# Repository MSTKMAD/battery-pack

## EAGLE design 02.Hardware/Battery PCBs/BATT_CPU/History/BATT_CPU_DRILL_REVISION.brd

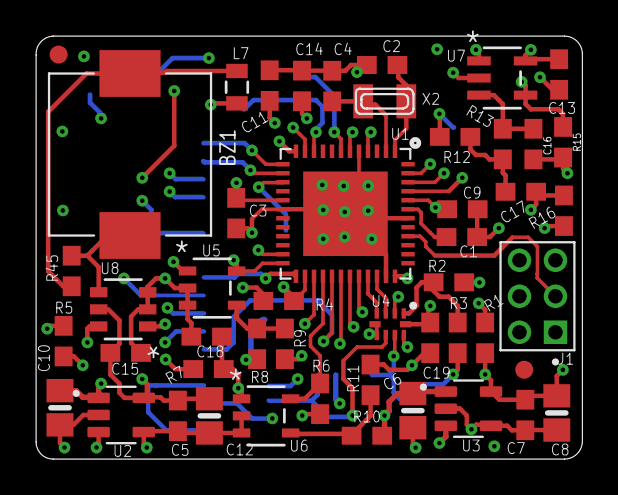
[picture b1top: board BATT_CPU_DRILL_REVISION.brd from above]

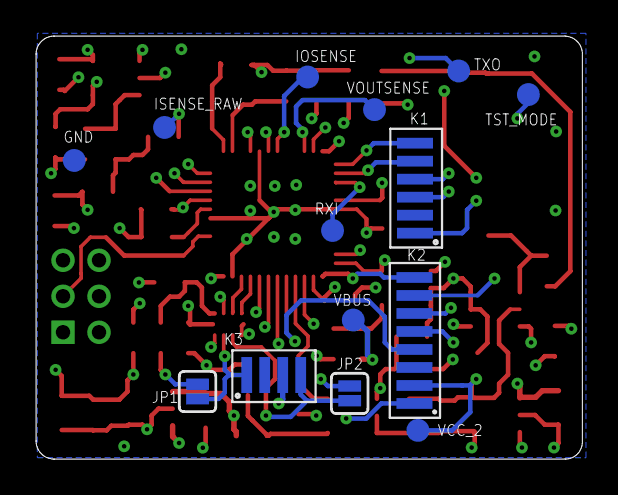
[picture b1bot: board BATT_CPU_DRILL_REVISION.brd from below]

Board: 4 copper layers, 30.4 x 23.5 mm, 63 parts (14 on the bottom side), 44 nets.

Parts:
BZ1: PKMCS0909E4000-R1; PKMCS0909
C1, C14: 2.2uF; 0603-NO
C2, C4: 22pF; 0603-NO
C3, C5, C7, C9, C11, C13, C15, C18, C19: 100n; 0603-NO
C6, C8, C10, C12: 2.2uF; 0805-NO
C16, C17: 1u; 0603-NO
GND: TESTPAD_TPSQB1,27; TESTPAD_B1,27
IOSENSE: TESTPAD_TPSQB1,27; TESTPAD_B1,27
ISENSE_RAW: TESTPAD_TPSQB1,27; TESTPAD_B1,27
J1: 2314820-6; TE_2314820-6
JP1, JP2: JUMPER-SMT_2_NO_SILK; SMT-JUMPER_2_NO_SILK
K1: FLEX_DISPL; FLEX6
K2: FLEX_DCDC; FLEX8
K3: FLEX_CONN; FLEX4
L7: MMZ2012Y202BT000; 0805
R1, R2: 2k2; 0603
R3, R4: 100R; 0603
R5: 100k; 0603
R6, R7, R8, R10: 120k; 0603
R9: 5.6k; 0603
R11: 8.2k; 0603
R12, R15: 2.4k; 0603
R13: 62k; 0603
R16: 36k; 0603
R45: 330; 0603
RXI: TESTPAD_TPSQB1,27; TESTPAD_B1,27
TST_MODE: TESTPAD_TPSQB1,27; TESTPAD_B1,27
TXO: TESTPAD_TPSQB1,27; TESTPAD_B1,27
U1: ATSAMD21G18_QFN; TQFN48_7MM
U2, U3: TPS78230DDCR; SOT95P280X110-5N
U4: TS3USB221A; QFN-10-RSE
U5, U6: MAX9062EUK+T; 21-0057F_MXM
U7: MCP6071T-E/OT; SOT-23-5_MC_MCH
U8: SN74LVC1G19DBVR; DBV6
U$34, U$35: FIDUCIAL""; FIDUCIAL_1MM
VBUS: TESTPAD_TPSQB1,27; TESTPAD_B1,27
VCC_2: TESTPAD_TPSQB1,27; TESTPAD_B1,27
VOUTSENSE: TESTPAD_TPSQB1,27; TESTPAD_B1,27
X2: 32.768; XTAL3215

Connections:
!RESET: J1.3, U1.40
#EN_DCDC: K2.8, U1.25
/FLAG_BATTLOW: R6.1, U1.28, U6.5
AREF: C14.1, U1.4
BUZZER: U1.23, U8.1
D+: U1.34, U4.3
D-: U1.33, U4.4
EN_VCC2: R5.2, U2.3
FLAG_CHRG: R7.1, U1.24, U5.5
GND: C1.2, C2.2, C3.2, C4.2, C5.2, C6.2, C7.2, C8.2, C9.2, C10.2, C11.2, C12.2, C13.2, C14.2, C15.2, C16.2, C18.2, C19.2, GND.TP, J1.5, K1.2, K2.3, K3.2, R5.1, R9.2, R11.2, R15.2, U1.5, U1.18, U1.35, U1.42, U1.THERMAL, U2.2, U2.4, U3.2, U3.4, U4.5, U4.6, U5.2, U5.3, U6.2, U6.3, U7.2, U8.2, U8.3
IOSENSE: C17.2, IOSENSE.TP, R16.1, U1.7, U1.47, U7.1
ISENSE_RAW: ISENSE_RAW.TP, K2.5, R12.2
unnamed: R15.1, R16.2, U7.4
unnamed: R2.1, R3.1, U4.1
unnamed: R1.1, R4.1, U4.2
unnamed: C2.1, U1.1, X2.P$1
unnamed: C4.1, U1.2, X2.P$2
unnamed: C17.1, R12.1, R13.2
unnamed: R10.1, R11.1, U6.4
unnamed: R8.1, R9.1, U5.4
unnamed: C16.1, R13.1, U7.3
unnamed: L7.1, U8.6
unnamed: BZ1.1, L7.2, R45.1
unnamed: BZ1.2, R45.2, U8.4
OP_SWITCH: K2.4, U1.29
RXI: RXI.TP, U1.15
SCL: K1.4, K2.6, U1.32
SCL2_CPU: JP2.1, R4.2, U1.26
SCL_2: JP2.2, K3.4, U4.7
SDA: K1.3, K2.1, U1.31
SDA2_CPU: JP1.1, R3.2, U1.27
SDA_2: JP1.2, K3.1, U4.8
SWCLK: J1.4, U1.45
SWDIO: J1.2, U1.46
S_DOWN: K1.6, U1.13
S_UP: K1.5, U1.14
TST_MODE: TST_MODE.TP, U1.12
TXO: TXO.TP, U1.11
USB_SEL: U1.30, U4.9
VBUS: C6.1, C10.1, K3.3, R8.2, R10.2, U2.1, U3.1, U3.3, VBUS.TP
VCC: C3.1, C7.1, C8.1, C9.1, C11.1, C18.1, C19.1, J1.1, R1.2, R2.2, R6.2, R7.2, U1.6, U1.17, U1.36, U1.44, U3.5, U4.10, U5.1, U6.1
VCC_2: C5.1, C12.1, C13.1, C15.1, K1.1, K2.2, U2.5, U7.5, U8.5, VCC_2.TP
VDDCORE: C1.1, U1.43
VOUTSENSE: K2.7, U1.10, VOUTSENSE.TP

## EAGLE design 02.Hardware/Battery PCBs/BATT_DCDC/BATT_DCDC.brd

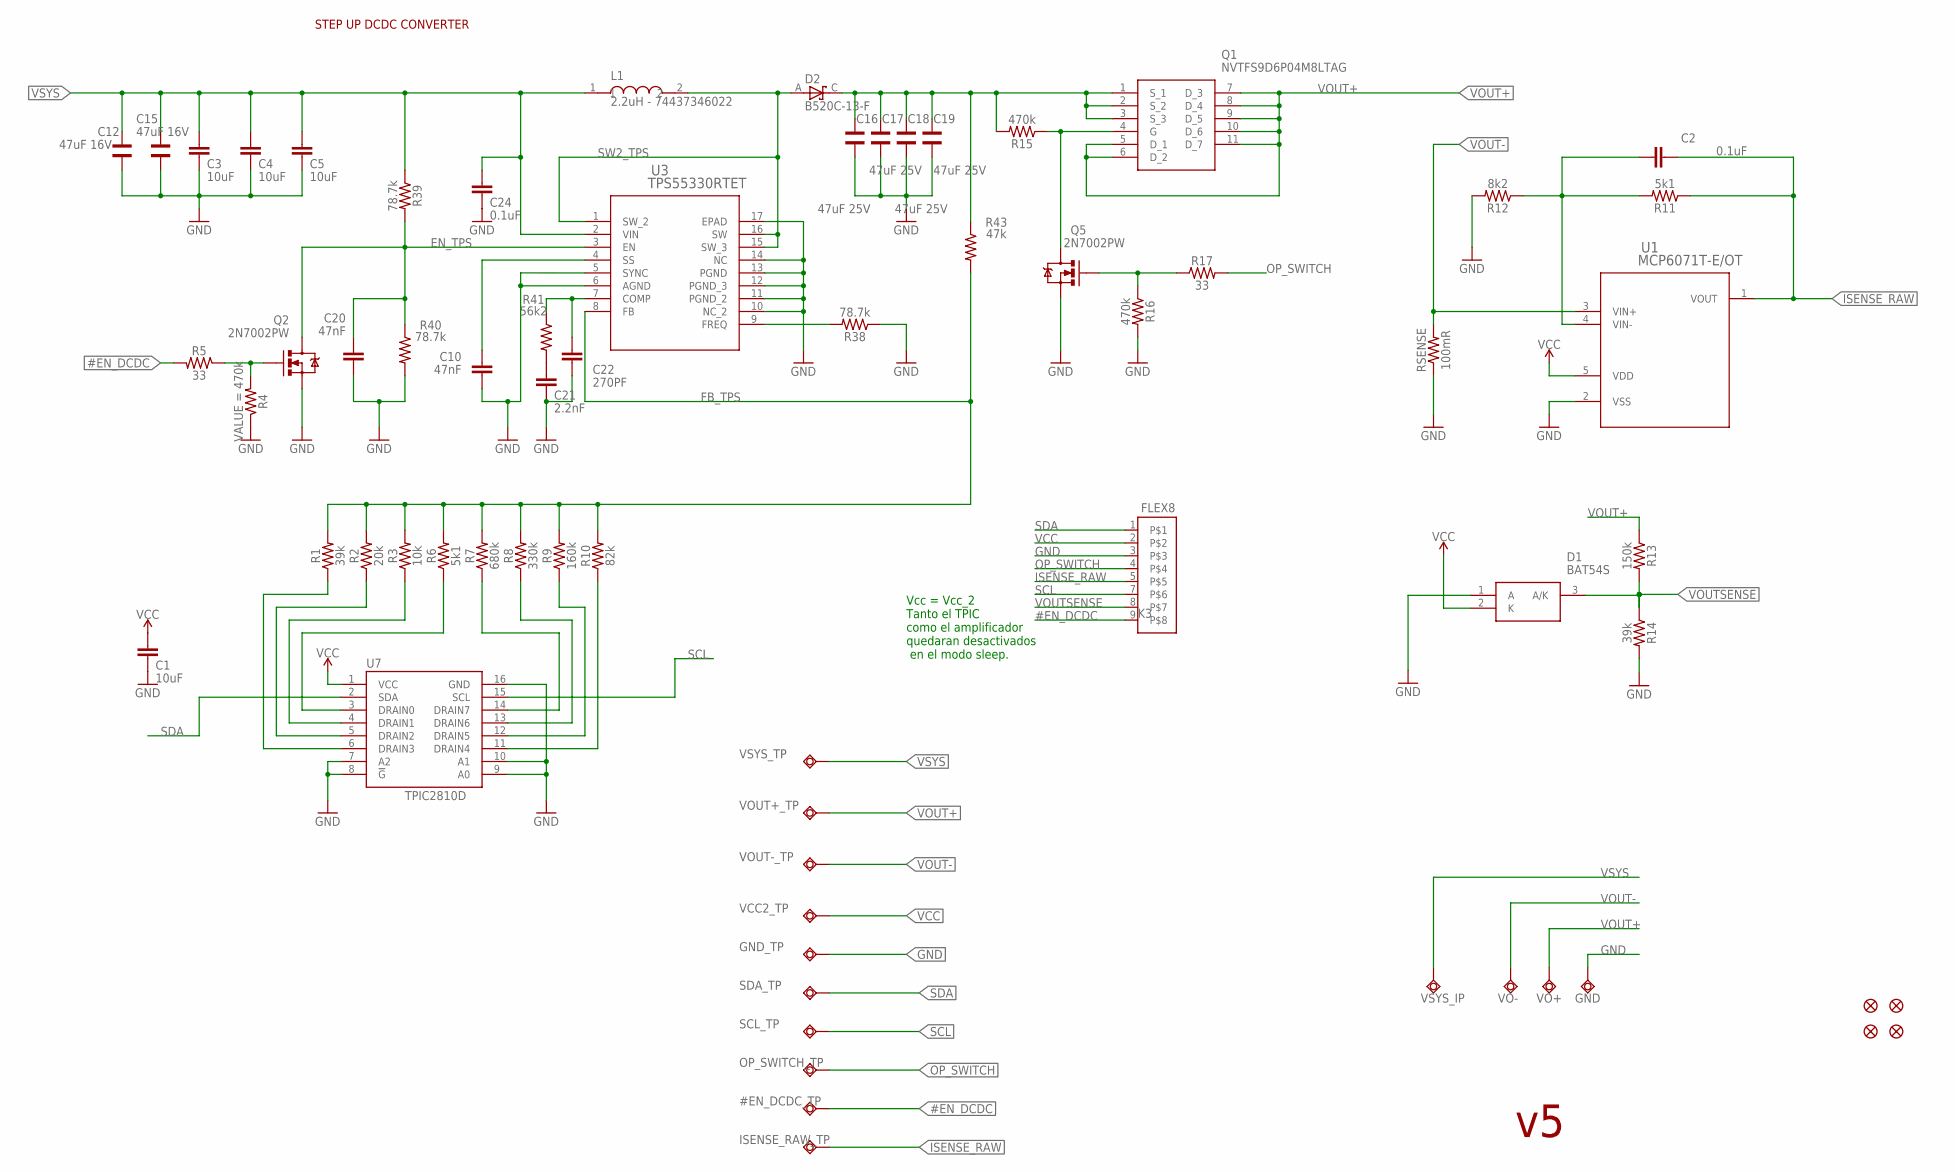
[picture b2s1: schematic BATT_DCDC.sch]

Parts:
#EN_DCDC_TP: TESTPAD_TPSQB1,27; TESTPAD_B1,27
C1, C3, C4, C5: 10uF; 0805
C2, C24: 0.1uF; 0603
C10, C20: 47nF; 0603
C12, C15: 47uF 16V; WCAP-CSGP_1210
C16, C17, C18, C19: 47uF 25V; WCAP-CSGP_1210
C21: 2.2nF; 0603
C22: 270PF; 0603
D1: BAT54S; SOT95P240X110-3N
D2: B520C-13-F; DIOM7959X250N
GND: TESTPAD_TPSQTP15SQ; TESTPAD_TP15SQ
GND_TP: TESTPAD_TPSQB1,27; TESTPAD_B1,27
ISENSE_RAW_TP: TESTPAD_TPSQB1,27; TESTPAD_B1,27
K3: FLEX8
L1: 2.2uH - 74437346022; INDM7366X500
OP_SWITCH_TP: TESTPAD_TPSQB1,27; TESTPAD_B1,27
Q1: NVTFS9D6P04M8LTAG; NVTFS5124PLTWG
Q2, Q5: 2N7002PW; SOT323
R1, R14: 39k; 0402
R2: 20k; 0402
R3: 10k; 0402
R4, R15, R16: 470k; 0402
R5, R17: 33; 0402
R6, R11: 5k1; 0402
R7: 680k; 0402
R8: 330k; 0402
R9: 160k; 0402
R10: 82k; 0402
R12: 8k2; 0402
R13: 150k; 0402
R38, R39, R40: 78.7k; 0402
R41: 56k2; 0402
R43: 47k; 0402
RSENSE: 100mR; 0603
SCL_TP: TESTPAD_TPSQB1,27; TESTPAD_B1,27
SDA_TP: TESTPAD_TPSQB1,27; TESTPAD_B1,27
U1: MCP6071T-E/OT; SOT-23-5_MC_MCH
U3: TPS55330RTET; RTE16_1P66X1P66_TEX
U7: TPIC2810D; SO16
U$1, U$2, U$34, U$35: FIDUCIAL""; FIDUCIAL_1MM
VCC2_TP: TESTPAD_TPSQB1,27; TESTPAD_B1,27
VO+: TESTPAD_TPSQTP15SQ; TESTPAD_TP15SQ
VO-: TESTPAD_TPSQTP15SQ; TESTPAD_TP15SQ
VOUT+_TP: TESTPAD_TPSQB1,27; TESTPAD_B1,27
VOUT-_TP: TESTPAD_TPSQB1,27; TESTPAD_B1,27
VSYS_IP: TESTPAD_TPSQTP15SQ; TESTPAD_TP15SQ
VSYS_TP: TESTPAD_TPSQB1,27; TESTPAD_B1,27

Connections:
#EN_DCDC: #EN_DCDC_TP.TP, K3.9, R5.2
COMP_TPS: C22.2, R41.1, U3.7 (COMP)
EN_TPS: C20.1, Q2.3 (D), R39.2, R40.1, U3.3 (EN)
FB_TPS: R1.2, R2.2, R3.2, R6.2, R7.2, R8.2, R9.2, R10.2, R43.2, U3.8 (FB)
FREQ_TPS: R38.2, U3.9 (FREQ)
GND: C1.1, C3.1, C4.1, C5.1, C10.2, C12.1, C15.1, C16.1, C17.1, C18.1, C19.1, C20.2, C21.1, C22.1, C24.1, D1.1 (A), GND.TP, GND_TP.TP, K3.3, Q2.2 (S), Q5.2 (S), R4.1, R12.2, R14.2, R16.2, R38.1, R40.2, RSENSE.1, U1.2 (VSS), U3.5 (SYNC), U3.6 (AGND), U3.10 (NC_2), U3.11 (PGND_2), U3.12 (PGND_3), U3.13 (PGND), U3.14 (NC), U3.17 (EPAD), U7.7 (A2), U7.8 (!G), U7.9 (A0), U7.10 (A1), U7.16 (GND)
ISENSE_RAW: C2.1, ISENSE_RAW_TP.TP, K3.5, R11.1, U1.1 (VOUT)
unnamed: C2.2, R11.2, R12.1, U1.4 (VIN-)
unnamed: R1.1, U7.6 (DRAIN3)
unnamed: R2.1, U7.5 (DRAIN2)
unnamed: Q2.1 (G), R4.2, R5.1
unnamed: R3.1, U7.4 (DRAIN1)
unnamed: R6.1, U7.3 (DRAIN0)
unnamed: R7.1, U7.14 (DRAIN7)
unnamed: Q1.4 (G), Q5.3 (D), R15.1
unnamed: R8.1, U7.13 (DRAIN6)
unnamed: R9.1, U7.12 (DRAIN5)
unnamed: R10.1, U7.11 (DRAIN4)
unnamed: Q5.1 (G), R16.1, R17.1
unnamed: C10.1, U3.4 (SS)
unnamed: C21.2, R41.2
OP_SWITCH: K3.4, OP_SWITCH_TP.TP, R17.2
SCL: K3.7, SCL_TP.TP, U7.15 (SCL)
SDA: K3.1, SDA_TP.TP, U7.2 (SDA)
SW2_TPS: D2.A, L1.2, U3.1 (SW_2), U3.15 (SW_3), U3.16 (SW)
VCC: C1.2, D1.2 (K), K3.2, U1.5 (VDD), U7.1 (VCC), VCC2_TP.TP
VOUT+: Q1.5 (D_1), Q1.6 (D_2), Q1.7 (D_3), Q1.8 (D_4), Q1.9 (D_5), Q1.10 (D_6), Q1.11 (D_7), R13.1, VO+.TP, VOUT+_TP.TP
VOUT-: RSENSE.2, U1.3 (VIN+), VO-.TP, VOUT-_TP.TP
VOUTSENSE: D1.3 (A/K), K3.8, R13.2, R14.1
VSOURCE: C16.2, C17.2, C18.2, C19.2, D2.C, Q1.1 (S_1), Q1.2 (S_2), Q1.3 (S_3), R15.2, R43.1
VSYS: C3.2, C4.2, C5.2, C12.2, C15.2, C24.2, L1.1, R39.1, U3.2 (VIN), VSYS_IP.TP, VSYS_TP.TP

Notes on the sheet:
STEP UP DCDC CONVERTER
Vcc = Vcc_2 Tanto el TPIC como el amplificador quedaran desactivados en el modo sleep.

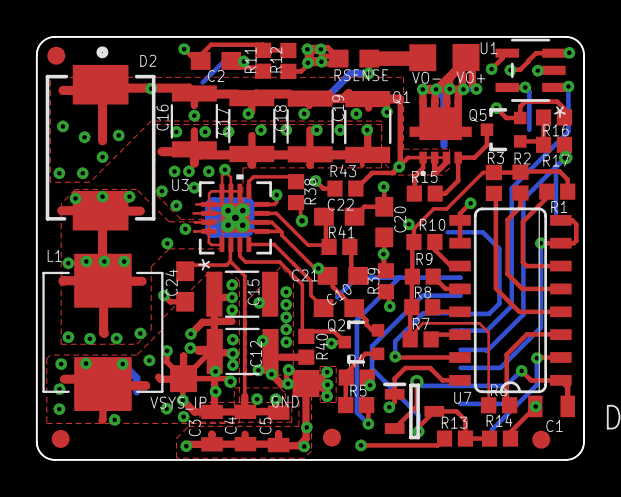
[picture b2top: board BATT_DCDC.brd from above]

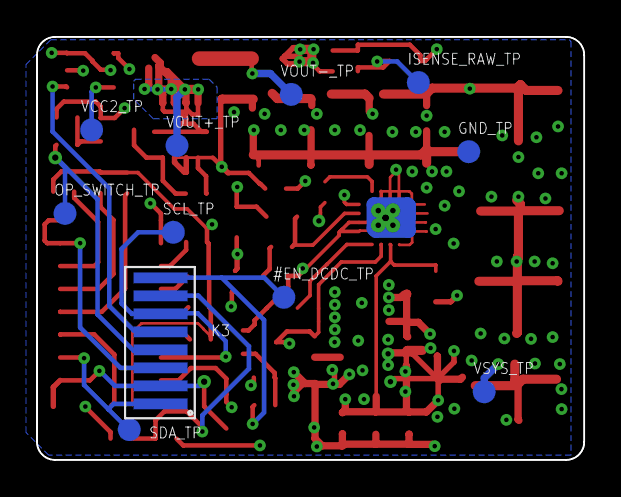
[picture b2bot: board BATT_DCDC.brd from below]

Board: 4 copper layers, 30.4 x 23.5 mm, 67 parts (11 on the bottom side), 31 nets.

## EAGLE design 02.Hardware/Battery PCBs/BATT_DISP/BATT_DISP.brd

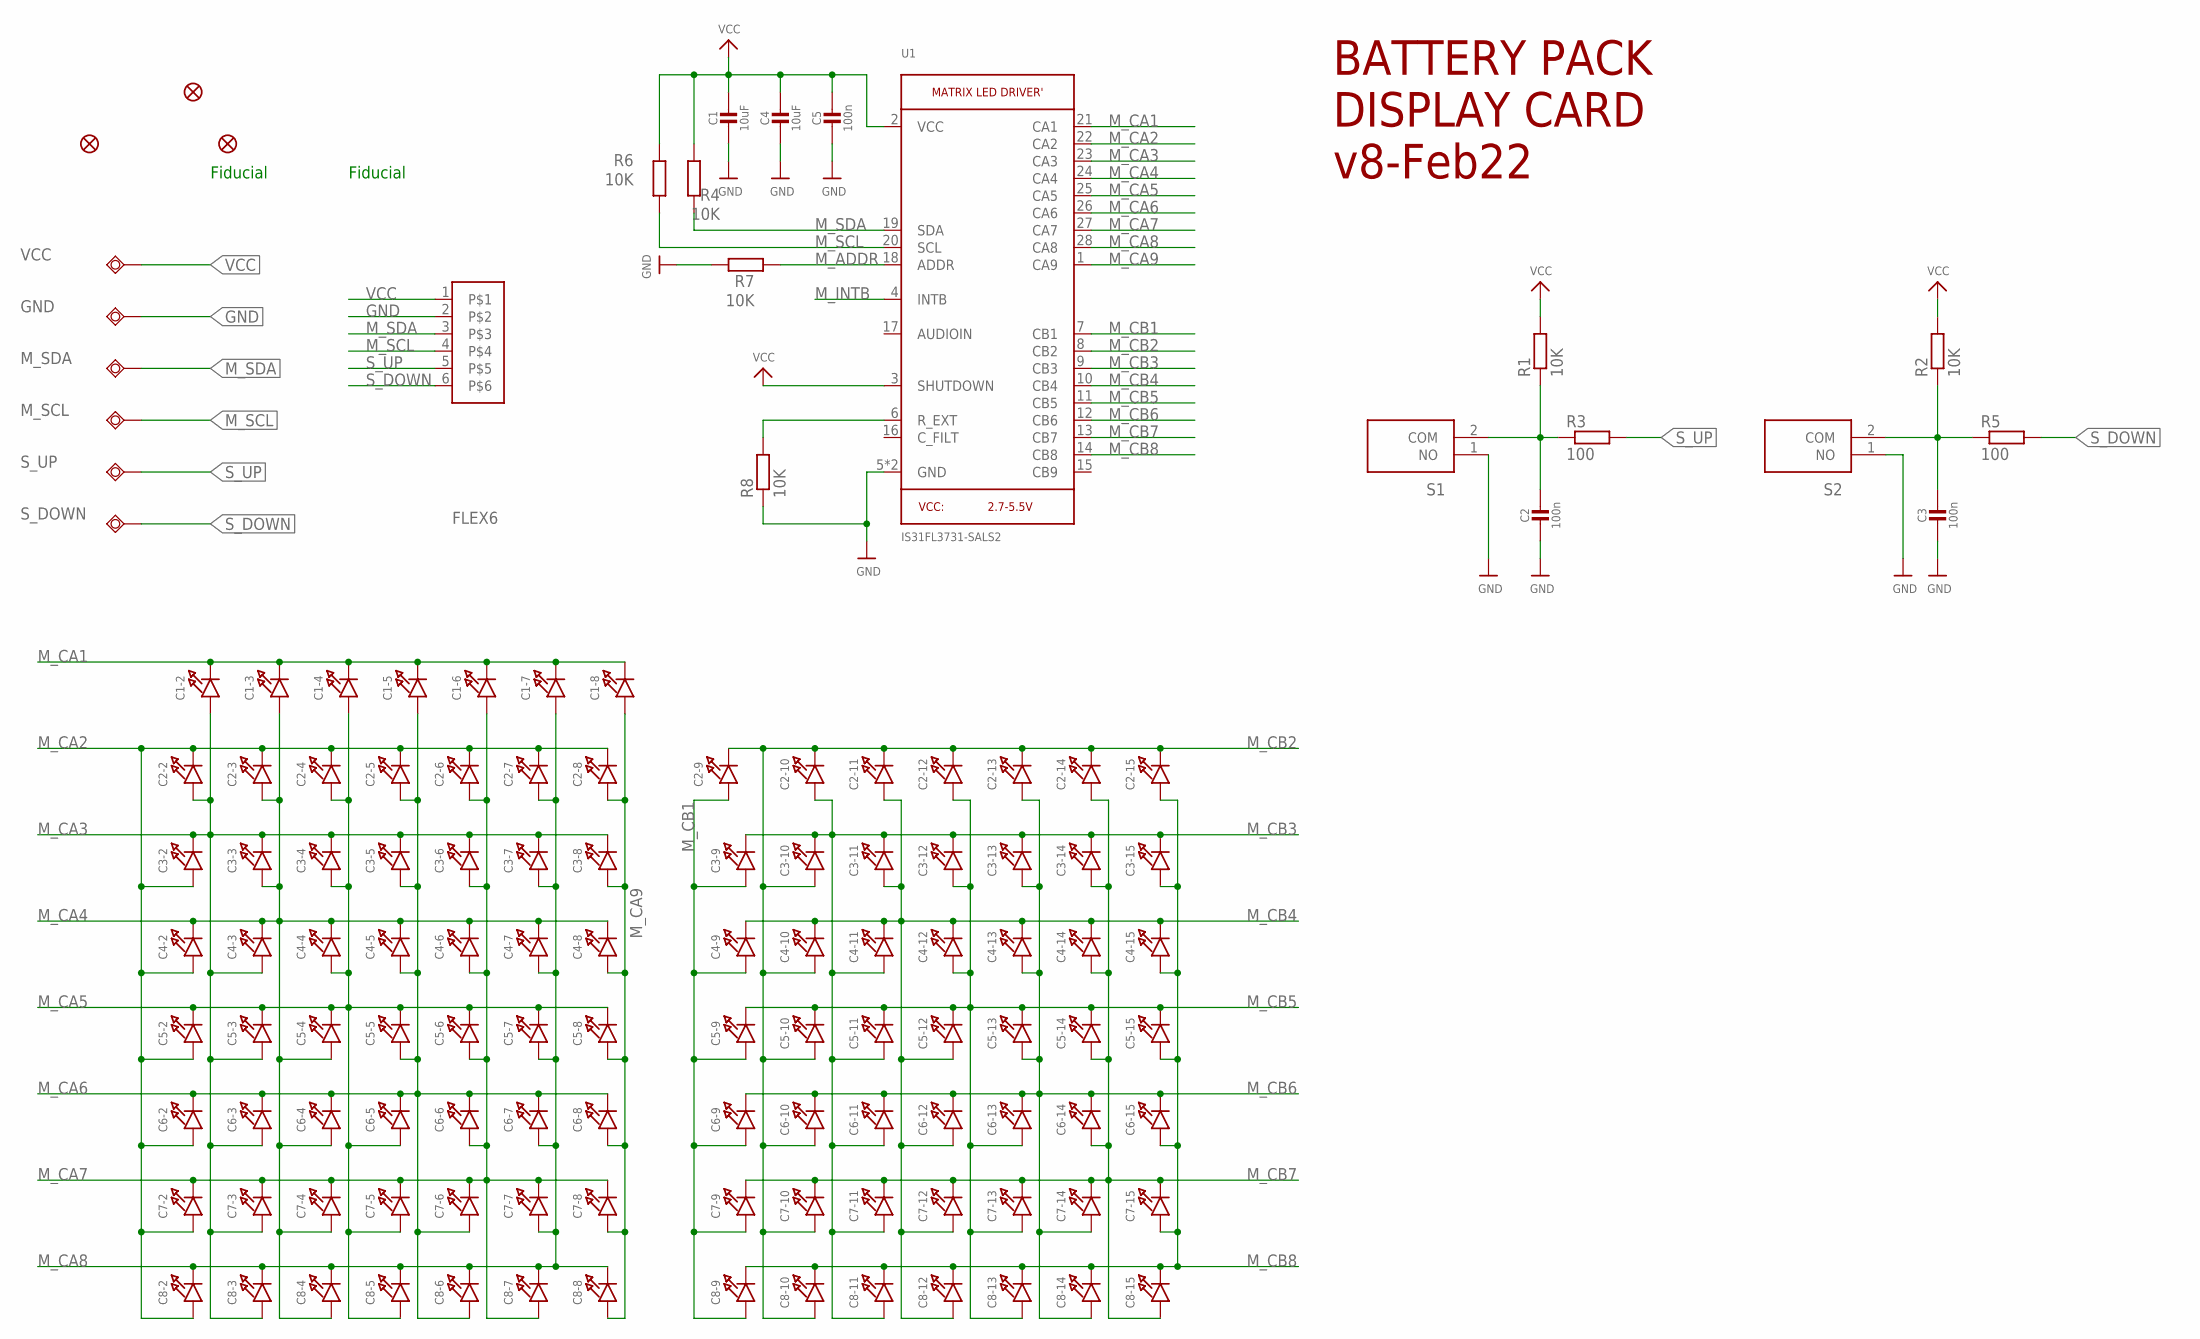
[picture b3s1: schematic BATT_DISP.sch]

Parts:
C1, C4: 10uF; 0805-NO
C1-2, C1-3, C1-4, C1-5, C1-6, C1-7, C1-8, C2-2, C2-3, C2-4, C2-5, C2-6, C2-7, C2-8, C2-9, C2-10, C2-11, C2-12, C2-13, C2-14, C2-15, C3-2, C3-3, C3-4, C3-5, C3-6, C3-7, C3-8, C3-9, C3-10, C3-11, C3-12, C3-13, C3-14, C3-15, C4-2, C4-3, C4-4, C4-5, C4-6, C4-7, C4-8, C4-9, C4-10, C4-11, C4-12, C4-13, C4-14, C4-15, C5-2, C5-3, C5-4, C5-5, C5-6, C5-7, C5-8, C5-9, C5-10, C5-11, C5-12, C5-13, C5-14, C5-15, C6-2, C6-3, C6-4, C6-5, C6-6, C6-7, C6-8, C6-9, C6-10, C6-11, C6-12, C6-13, C6-14, C6-15, C7-2, C7-3, C7-4, C7-5, C7-6, C7-7, C7-8, C7-9, C7-10, C7-11, C7-12, C7-13, C7-14, C7-15, C8-2, C8-3, C8-4, C8-5, C8-6, C8-7, C8-8, C8-9, C8-10, C8-11, C8-12, C8-13, C8-14, C8-15: LED0402_NOOUTLINE; CHIPLED_0402_NOOUTLINE
C2, C3, C5: 100n; 0805-NO
FD1: FIDUCIALUFIDUCIAL; FIDUCIAL-MICRO
FD2, FD3: FIDUCIAL""; FIDUCIAL_1MM
GND: TESTPAD_TPSQB1,27; TESTPAD_B1,27
K1: FLEX6
M_SCL: TESTPAD_TPSQB1,27; TESTPAD_B1,27
M_SDA: TESTPAD_TPSQB1,27; TESTPAD_B1,27
R1, R2, R4, R6, R7, R8: 10K; R0603
R3, R5: 100; R0603
S1, S2: KXT311LHS
S_DOWN: TESTPAD_TPSQB1,27; TESTPAD_B1,27
S_UP: TESTPAD_TPSQB1,27; TESTPAD_B1,27
U1: IS31FL3731-SALS2; QFN28_4MM_0.4MM
VCC: TESTPAD_TPSQB1,27; TESTPAD_B1,27

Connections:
GND: C1.2, C2.2, C3.2, C4.2, C5.2, GND.TP, K1.2, R7.2, R8.1, S1.1 (NO), S2.1 (NO), U1.5 (GND), U1.THERMAL (GND)
M_ADDR: R7.1, U1.18 (ADDR)
M_CA1: C1-2.C, C1-3.C, C1-4.C, C1-5.C, C1-6.C, C1-7.C, C1-8.C, U1.21 (CA1)
M_CA2: C2-2.C, C2-3.C, C2-4.C, C2-5.C, C2-6.C, C2-7.C, C2-8.C, C3-2.A, C4-2.A, C5-2.A, C6-2.A, C7-2.A, C8-2.A, U1.22 (CA2)
M_CA3: C1-2.A, C2-2.A, C3-2.C, C3-3.C, C3-4.C, C3-5.C, C3-6.C, C3-7.C, C3-8.C, C4-3.A, C5-3.A, C6-3.A, C7-3.A, C8-3.A, U1.23 (CA3)
M_CA4: C1-3.A, C2-3.A, C3-3.A, C4-2.C, C4-3.C, C4-4.C, C4-5.C, C4-6.C, C4-7.C, C4-8.C, C5-4.A, C6-4.A, C7-4.A, C8-4.A, U1.24 (CA4)
M_CA5: C1-4.A, C2-4.A, C3-4.A, C4-4.A, C5-2.C, C5-3.C, C5-4.C, C5-5.C, C5-6.C, C5-7.C, C5-8.C, C6-5.A, C7-5.A, C8-5.A, U1.25 (CA5)
M_CA6: C1-5.A, C2-5.A, C3-5.A, C4-5.A, C5-5.A, C6-2.C, C6-3.C, C6-4.C, C6-5.C, C6-6.C, C6-7.C, C6-8.C, C7-6.A, C8-6.A, U1.26 (CA6)
M_CA7: C1-6.A, C2-6.A, C3-6.A, C4-6.A, C5-6.A, C6-6.A, C7-2.C, C7-3.C, C7-4.C, C7-5.C, C7-6.C, C7-7.C, C7-8.C, C8-7.A, U1.27 (CA7)
M_CA8: C1-7.A, C2-7.A, C3-7.A, C4-7.A, C5-7.A, C6-7.A, C7-7.A, C8-2.C, C8-3.C, C8-4.C, C8-5.C, C8-6.C, C8-7.C, C8-8.C, U1.28 (CA8)
M_CA9: C1-8.A, C2-8.A, C3-8.A, C4-8.A, C5-8.A, C6-8.A, C7-8.A, C8-8.A, U1.1 (CA9)
M_CB1: C2-9.A, C3-9.A, C4-9.A, C5-9.A, C6-9.A, C7-9.A, C8-9.A, U1.7 (CB1)
M_CB2: C2-9.C, C2-10.C, C2-11.C, C2-12.C, C2-13.C, C2-14.C, C2-15.C, C3-10.A, C4-10.A, C5-10.A, C6-10.A, C7-10.A, C8-10.A, U1.8 (CB2)
M_CB3: C2-10.A, C3-9.C, C3-10.C, C3-11.C, C3-12.C, C3-13.C, C3-14.C, C3-15.C, C4-11.A, C5-11.A, C6-11.A, C7-11.A, C8-11.A, U1.9 (CB3)
M_CB4: C2-11.A, C3-11.A, C4-9.C, C4-10.C, C4-11.C, C4-12.C, C4-13.C, C4-14.C, C4-15.C, C5-12.A, C6-12.A, C7-12.A, C8-12.A, U1.10 (CB4)
M_CB5: C2-12.A, C3-12.A, C4-12.A, C5-9.C, C5-10.C, C5-11.C, C5-12.C, C5-13.C, C5-14.C, C5-15.C, C6-13.A, C7-13.A, C8-13.A, U1.11 (CB5)
M_CB6: C2-13.A, C3-13.A, C4-13.A, C5-13.A, C6-9.C, C6-10.C, C6-11.C, C6-12.C, C6-13.C, C6-14.C, C6-15.C, C7-14.A, C8-14.A, U1.12 (CB6)
M_CB7: C2-14.A, C3-14.A, C4-14.A, C5-14.A, C6-14.A, C7-9.C, C7-10.C, C7-11.C, C7-12.C, C7-13.C, C7-14.C, C7-15.C, C8-15.A, U1.13 (CB7)
M_CB8: C2-15.A, C3-15.A, C4-15.A, C5-15.A, C6-15.A, C7-15.A, C8-9.C, C8-10.C, C8-11.C, C8-12.C, C8-13.C, C8-14.C, C8-15.C, U1.14 (CB8)
M_INTB: U1.4 (INTB)
M_SCL: K1.4, M_SCL.TP, R6.1, U1.20 (SCL)
M_SDA: K1.3, M_SDA.TP, R4.1, U1.19 (SDA)
unnamed: C3.1, R2.1, R5.1, S2.2 (COM)
unnamed: C2.1, R1.1, R3.1, S1.2 (COM)
R_EXT: R8.2, U1.6 (R_EXT)
S_DOWN: K1.6, R5.2, S_DOWN.TP
S_UP: K1.5, R3.2, S_UP.TP
VCC: C1.1, C4.1, C5.1, K1.1, R1.2, R2.2, R4.2, R6.2, U1.2 (VCC), U1.3 (SHUTDOWN), VCC.TP

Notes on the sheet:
Fiducial
BATTERY PACK DISPLAY CARD v8-Feb22

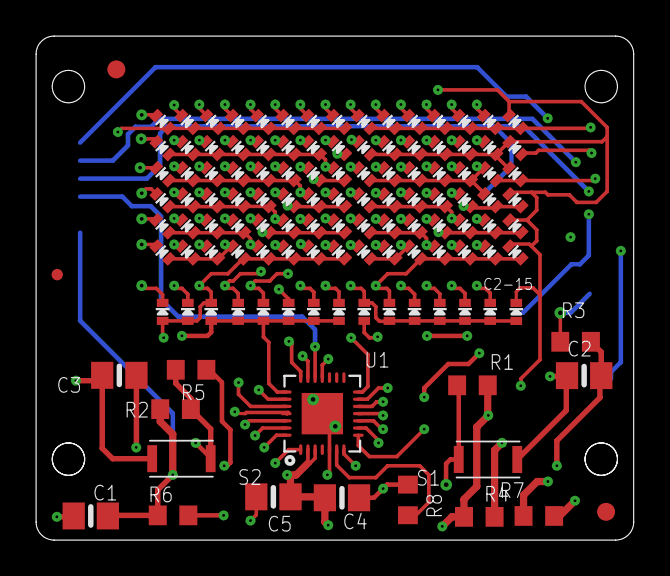
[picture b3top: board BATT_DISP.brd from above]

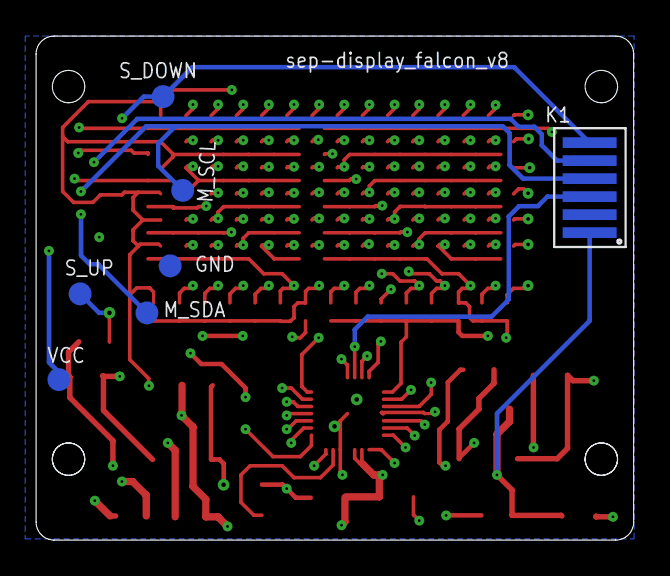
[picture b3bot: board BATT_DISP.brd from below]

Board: 4 copper layers, 33.2 x 28.0 mm, 131 parts (7 on the bottom side), 27 nets.

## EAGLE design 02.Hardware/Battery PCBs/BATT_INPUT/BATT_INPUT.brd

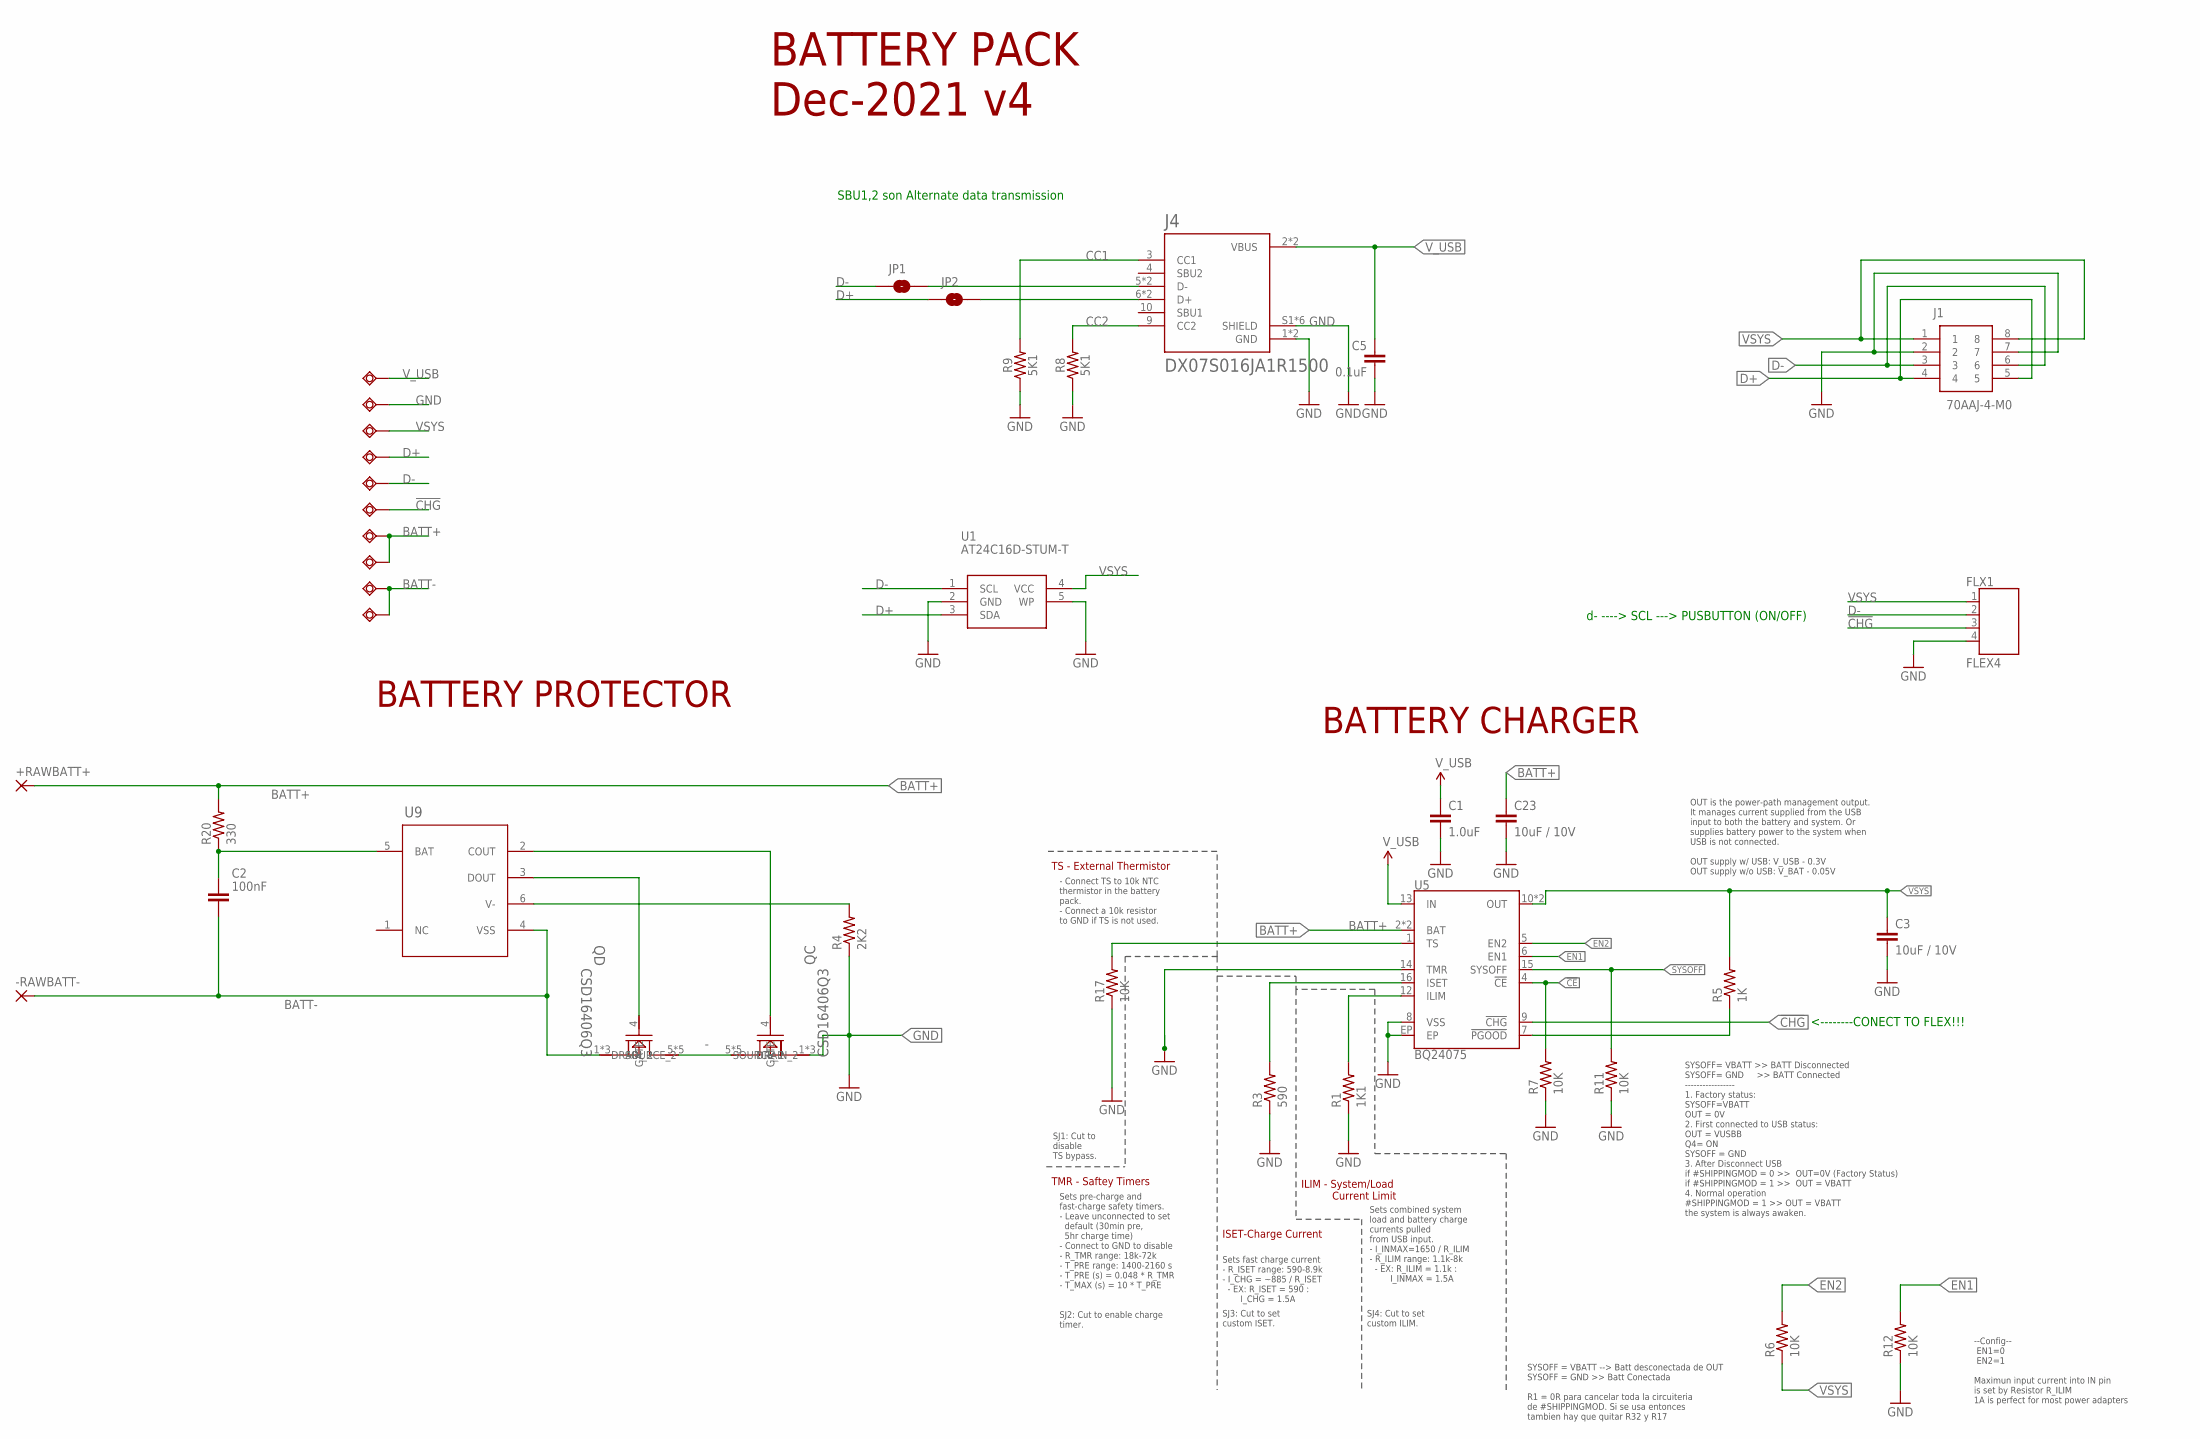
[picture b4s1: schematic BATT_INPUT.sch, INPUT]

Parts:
!CHG!: TESTPAD_TPSQB1,27; TESTPAD_B1,27
+RAWBATT+: SMD5; SMD2,54-5,08
-RAWBATT-: SMD5; SMD2,54-5,08
BATT+1, BATT+2: TESTPAD_TPSQB1,27; TESTPAD_B1,27
BATT-1, BATT-2: TESTPAD_TPSQB1,27; TESTPAD_B1,27
C1: 1.0uF; 0603
C2: 100nF; CAPC1608X85
C3, C23: 10uF / 10V; 0805-CAP
C5: 0.1uF; 0603
D+: TESTPAD_TPSQB1,27; TESTPAD_B1,27
D-: TESTPAD_TPSQB1,27; TESTPAD_B1,27
FLX1: FLEX4
GND: TESTPAD_TPSQB1,27; TESTPAD_B1,27
J1: 70AAJ-4-M0; 70AAJ4M0
J4: DX07S016JA1R1500; JAE_DX07S016JA1R1500
JP1, JP2: JUMPER-SMT_2_NO_SILK; SMT-JUMPER_2_NO_SILK
QC: CSD16406Q3; DQG0008A
QD: CSD16406Q3; DQG0008A
R1: 1K1; 0402
R3: 590; 0402
R4: 2K2; 0402
R5: 1K; 0402
R6, R7, R11, R12, R17: 10K; 0402
R8, R9: 5K1; 0402
R20: 330; 0402
U1: AT24C16D-STUM-T; SOT95P280X100-5N
U5: BQ24075; PVQFN-N16
U9: Value; DSE0006A
VSYS: TESTPAD_TPSQB1,27; TESTPAD_B1,27
V_USB: TESTPAD_TPSQB1,27; TESTPAD_B1,27

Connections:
!CE!: R7.2, U5.4 (!CE!)
!CHG!: !CHG!.TP, FLX1.3, U5.9 (!CHG!)
-: QC.5 (DRAIN_2), QC.6 (DRAIN_2), QC.7 (DRAIN_2), QC.8 (DRAIN_2), QC.9 (DRAIN_2), QD.5 (DRAIN_2), QD.6 (DRAIN_2), QD.7 (DRAIN_2), QD.8 (DRAIN_2), QD.9 (DRAIN_2)
BATT+: +RAWBATT+.1, BATT+1.TP, BATT+2.TP, C23.1, R20.2, U5.2 (BAT), U5.3 (BAT)
BATT-: -RAWBATT-.1, BATT-1.TP, BATT-2.TP, C2.2, QD.1 (SOURCE_2), QD.2 (SOURCE_2), QD.3 (SOURCE_2), U9.4 (VSS)
CC1: J4.3 (CC1), R9.2
CC2: J4.9 (CC2), R8.2
D+: D+.TP, J1.4, J1.5, JP2.1, U1.3 (SDA)
D-: D-.TP, FLX1.2, J1.3, J1.6, JP1.1, U1.1 (SCL)
EN1: R12.2, U5.6 (EN1)
EN2: R6.2, U5.5 (EN2)
GND: C1.2, C3.2, C5.2, C23.2, FLX1.4, GND.TP, J1.2, J1.7, J4.1 (GND), J4.12 (GND), J4.S1 (SHIELD), J4.S2 (SHIELD), J4.S3 (SHIELD), J4.S4 (SHIELD), J4.S5 (SHIELD), J4.S6 (SHIELD), QC.1 (SOURCE_2), QC.2 (SOURCE_2), QC.3 (SOURCE_2), R1.1, R3.1, R4.1, R7.1, R8.1, R9.1, R11.1, R12.1, R17.1, U1.2 (GND), U1.5 (WP), U5.8 (VSS), U5.14 (TMR), U5.EP
ILIM: R1.2, U5.12 (ILIM)
ISET: R3.2, U5.16 (ISET)
unnamed: R5.1, U5.7 (!PGOOD!)
unnamed: J4.5 (D-), J4.8 (D-), JP1.2
unnamed: J4.6 (D+), J4.7 (D+), JP2.2
unnamed: C2.1, R20.1, U9.5 (BAT)
unnamed: R4.2, U9.6 (V-)
unnamed: QC.4 (GATE), U9.2 (COUT)
unnamed: QD.4 (GATE), U9.3 (DOUT)
SYSOFF: R11.2, U5.15 (SYSOFF)
TS1: R17.2, U5.1 (TS)
VSYS: C3.1, FLX1.1, J1.1, J1.8, R5.2, R6.1, U1.4 (VCC), U5.10 (OUT), U5.11 (OUT), VSYS.TP
V_USB: C1.1, C5.1, J4.2 (VBUS), J4.11 (VBUS), U5.13 (IN), V_USB.TP

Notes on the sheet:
BATTERY PACK Dec-2021 v4
Sets fast charge current - R_ISET range: 590-8.9k - I_CHG = ~885 / R_ISET - EX: R_ISET = 590 : I_CHG = 1.5A
Sets combined system load and battery charge currents pulled from USB input. - I_INMAX=1650 / R_ILIM - R_ILIM range: 1.1k-8k - EX: R_ILIM = 1.1k : I_INMAX = 1.5A
SJ1: Cut to disable TS bypass.
SJ3: Cut to set custom ISET.
SJ4: Cut to set custom ILIM.
ILIM - System/Load Current Limit
ISET-Charge Current
TMR - Saftey Timers
Sets pre-charge and fast-charge safety timers. - Leave unconnected to set default (30min pre, 5hr charge time) - Connect to GND to disable - R_TMR range: 18k-72k - T_PRE range: 1400-2160 s - T_PRE (s) = 0.048 * R_TMR - T_MAX (s) = 10 * T_PRE
SJ2: Cut to enable charge timer.
TS - External Thermistor
- Connect TS to 10k NTC thermistor in the battery pack. - Connect a 10k resistor to GND if TS is not used.
OUT is the power-path management output. It manages current supplied from the USB input to both the battery and system. Or supplies battery power to the system when USB is not connected. OUT supply w/ USB: V_USB - 0.3V OUT supply w/o USB: V_BAT - 0.05V
SYSOFF= VBATT >> BATT Disconnected SYSOFF= GND >> BATT Connected ----------------- 1. Factory status: SYSOFF=VBATT OUT = 0V 2. First connected to USB status: OUT = VUSBB Q4= ON SYSOFF = GND 3. After Disconnect USB if #SHIPPINGMOD = 0 >> OUT=0V (Factory Status) if #SHIPPINGMOD = 1 >> OUT = VBATT 4. 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
SYSOFF = VBATT --> Batt desconectada de OUT SYSOFF = GND >> Batt Conectada R1 = 0R para cancelar toda la circuiteria de #SHIPPINGMOD. Si se usa entonces tambien hay que quitar R32 y R17
--Config-- EN1=0 EN2=1 Maximun input current into IN pin is set by Resistor R_ILIM 1A is perfect for most power adapters
BATTERY PROTECTOR
BATTERY CHARGER
<--------CONECT TO FLEX!!!
d- ----> SCL ---> PUSBUTTON (ON/OFF)
SBU1,2 son Alternate data transmission

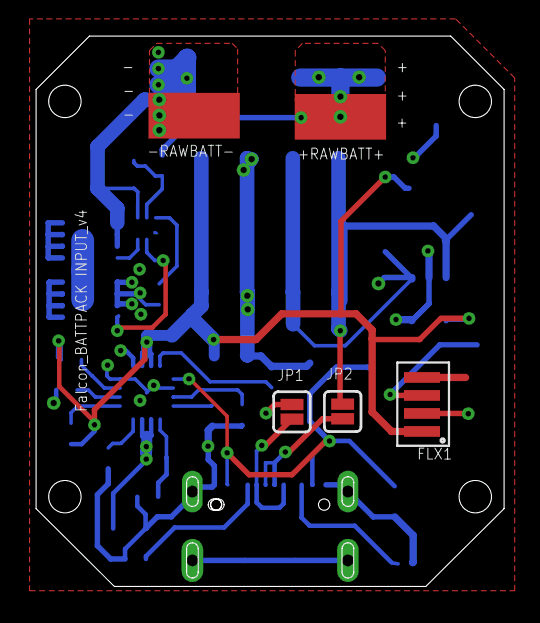
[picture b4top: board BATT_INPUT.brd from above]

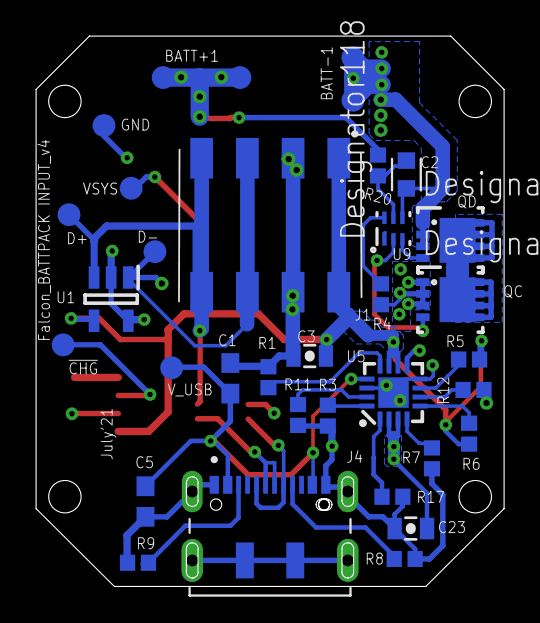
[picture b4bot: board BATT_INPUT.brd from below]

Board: 4 copper layers, 26.0 x 30.6 mm, 39 parts (34 on the bottom side), 25 nets.

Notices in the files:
parts and their libraries:
microbuilder: This work is placed in the public domain, and may be freely used for commercial and non-commercial work with the following conditions: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
SparkFun-Resistors: Licensing: Creative Commons ShareAlike 4.0 International - https://creativecommons.org/licenses/by-sa/4.0
